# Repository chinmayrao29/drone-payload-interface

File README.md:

# Drone Payload Interface

A plug-and-play USB-C interface for hot-swapping payload modules on a drone. The drone carries an **interface board**. Each payload is a self-contained **module** that plugs into it over USB-C. When a module is connected, the interface board identifies it, checks it's a known and valid module, and only then switches power on to it.

The first payload module is a **LoRa communications relay**.

## How module identification works

Each module is identified in two independent ways, and power is enabled only when they agree:

1. **Analog ID (CC1 line):** the interface board has a fixed pull-up resistor on CC1. Each module type has its own pull-down resistor, so each type produces a distinct CC1 voltage that the ESP32 reads with its ADC.
2. **Digital ID (EEPROM):** each module carries an I2C EEPROM holding a module profile record. The interface board reads it over the USB-C SBU1/SBU2 pins (used as I2C SDA/SCL).

If the two channels disagree, or either one is unreadable, the module is not powered.

## Repository layout

```
drone-payload-interface/
├── firmware/
│   ├── interface-board-esp32/   ESP32-S3 firmware (PlatformIO)
│   └── relay-module-stm32/      STM32F103 relay firmware (STM32CubeIDE)
├── hardware/
│   └── interface_board/         KiCad: interface board
│       ├── relay_module/        KiCad: LoRa relay module
│       ├── test_module/         KiCad: test module
│       └── libs/                Bundled custom footprints (shared)
├── tools/
│   └── eeprom-programmer/       Arduino sketch for writing module EEPROMs
├── raspberry-pi/                Companion computer code (to be added)
└── docs/                        Bring-up notes and project documentation
```

## Hardware

### Interface board

| Part | Role |
|---|---|
| ESP32-S3-WROOM-1 | Main controller: detection, ID validation, power control, comms |
| GCT USB4085-GF-A | USB-C receptacle that modules plug into |
| TPS2116 | Power mux |
| INA219 | Current/voltage monitoring of module power |
| AMS1117-3.3 | 3.3 V regulator for the board logic |

**Headers**

| Header | Pins | Use |
|---|---|---|
| J1 | 2-pin | Power input (5 V) |
| J4 | 4-pin: GND / +3V3 / UART_TX / UART_RX | Debug and flashing (ESP32 UART) |
| J3 | 4-pin, same pinout as J4 | Link to the Raspberry Pi |

### Relay module

| Part | Role |
|---|---|
| STM32F103C8T6 | Module controller |
| EBYTE E22-900M30S | SX1262-based LoRa radio, 868 MHz, up to 30 dBm |
| TLV62568 + SRP4020TA-2R2M | Buck converter for the module supply |
| AT24Cxx EEPROM | Module ID profile, read by the interface board |
| SMA connector | Antenna |

> ⚠️ **Never power the relay module without an antenna attached.** The E22-900M30S transmits at up to 30 dBm, and transmitting into an open connector can damage its power amplifier.

## Firmware

### Interface board (ESP32-S3, PlatformIO)

Source is in `firmware/interface-board-esp32/src/`:

| File | Purpose |
|---|---|
| `main.cpp` | Startup and main loop |
| `detection.cpp/.h` | Module detection and CC1 / EEPROM ID checks |
| `power.cpp/.h` | Module power switching and monitoring |
| `comms.cpp/.h` | Communication with the Raspberry Pi |

**Build:** open `firmware/interface-board-esp32` as a folder in VS Code with the PlatformIO extension, then click **Build (✓)**.

**Flash over J4** using a USB-to-TTL adapter (CP2102 or similar):

| Adapter | J4 |
|---|---|
| GND | GND (pin 1) |
| TXD | UART_RX (pin 4) |
| RXD | UART_TX (pin 3) |
| 3V3 / 5V | not connected (the board is powered from J1) |

J4 has no DTR/RTS lines, so the ESP32 can't be put into bootloader mode automatically. Hold **GPIO0 low while powering up** the board, release it, then click **Upload (→)** in PlatformIO.

Serial monitor: 115200 baud.

### Relay module (STM32F103, STM32CubeIDE)

The project is in `firmware/relay-module-stm32/`. It uses the STM32 HAL with USART1, I2C1, SPI1 (to the radio) and TIM2 (1 Hz heartbeat). Received LoRa packets are signalled to the MCU through an EXTI interrupt on the radio's DIO line. The SX126x driver is in `Core/` and `sx126x_driver/`.

**Open:** in STM32CubeIDE, use **File → Import → Existing Projects into Workspace**, select `firmware/relay-module-stm32`, and leave "Copy projects into workspace" unticked.

**Flash:** connect an ST-Link V2 to the module's SWD header (SWDIO, SWCLK, GND, 3V3), then use Run/Debug in CubeIDE, or load `Debug/Relay_module.elf` in STM32CubeProgrammer.

### EEPROM programmer

`tools/eeprom-programmer/` contains an Arduino sketch for writing module profile records to the module EEPROMs. Open the `.ino` in the Arduino IDE. Check that the EEPROM type set in the sketch matches the chip fitted on the module before writing.

## Hardware design files

KiCad projects are in `hardware/interface_board/`. Custom footprints are bundled in the repo:

- `libs/Custom.pretty`: USB4085 USB-C connector, SRP4020 inductor, logo
- `relay_module/libs/E22-900M30S`: E22 radio footprint, symbol and 3D model

These are referenced through each project's `fp-lib-table` with `${KIPRJMOD}` paths, so the projects open on any machine without extra library setup. Gerbers and BOM/placement files for manufacturing are in each board's folder.

## Working with this repo

KiCad's local history (`.history/`), build output (`Debug/`, `.pio/`) and backup folders are excluded by `.gitignore`.

```
git add .
git commit -m "Describe the change"
git push
```

## Status

- Relay module firmware builds and flashes over ST-Link.
- Interface board powers up from J1, and the 3.3 V rail is confirmed.
- Next: confirm the ESP32 boots over the J4 serial link, then flash the interface board firmware.

See `docs/bring-up-notes.md` for details.

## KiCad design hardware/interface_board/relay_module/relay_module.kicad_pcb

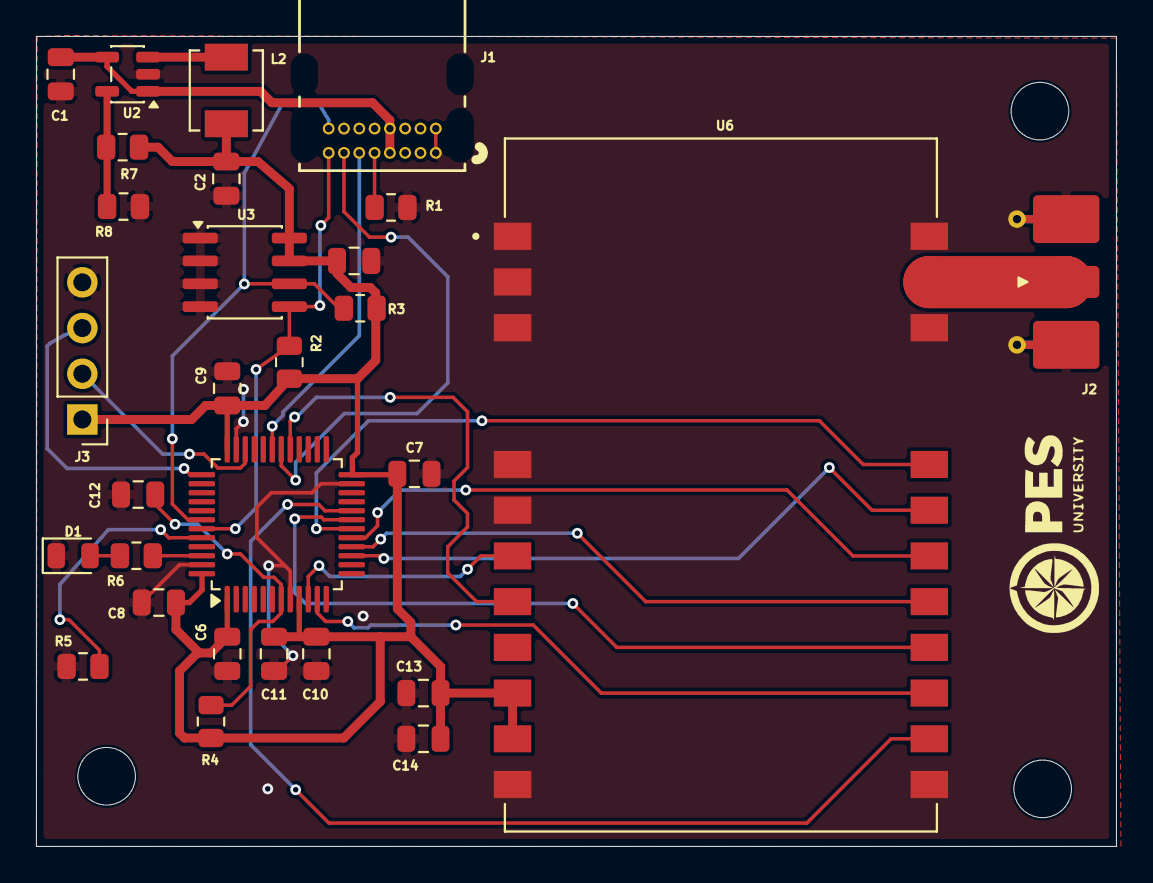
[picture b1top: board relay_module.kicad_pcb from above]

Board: 2 copper layers, 60.0 x 45.0 mm, 29 parts (0 on the bottom side), 26 nets.

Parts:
C1: 4.7u; C_0805_2012Metric
C2, C10, C13: 10u; C_0805_2012Metric
C5, C6, C7, C8, C9, C11, C12, C14: 100n; C_0805_2012Metric
D1: Green; LED_0805_2012Metric
J1: USB_C_Receptacle; CONN16_USB4085-GF-A_GCT
J2: SMA; SMA_Molex_73251-2120_EdgeMount_Horizontal
J3: Conn_01x04; PinHeader_1x04_P2.54mm_Vertical
L2: SRP4020TA-2R2M; IND_SRP4020TA-2R2M
R1: 220k; R_0805_2012Metric
R2, R3: 4.7k; R_0805_2012Metric
R4, R5, R8: 10k; R_0805_2012Metric
R6: 330; R_0805_2012Metric
R7: 33.2k; R_0805_2012Metric
U1: STM32F103C8Tx; LQFP-48_7x7mm_P0.5mm
U2: TLV62568DBV; SOT-23-5
U3: 24C02Cx-x-SN; SOIC-8_3.9x4.9mm_P1.27mm
U6: E22-900M30S; XCVR_E22-900M30S

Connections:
+3V3: C2.1, C5.1, C6.1, C7.1, C8.1, C9.1, C10.1, C11.1, C13.1, C14.1, J3.1, L2.2, R2.2, R3.2, R4.1, R7.2, U1.1 (VBAT), U1.9 (VDDA), U1.24 (VDD), U1.36 (VDD), U1.48 (VDD), U3.7 (WP), U3.8 (VCC), U6.9 (VCC), U6.10 (VCC)
/BUSY: U1.11 (PA1), U6.14 (BUSY)
/CC1_ID: J1.A5 (CC1), R1.1
/I2C_SCL: J1.B8 (SBU2), R3.1, U1.42 (PB6), U3.6 (SCL)
/I2C_SDA: J1.A8 (SBU1), R2.1, U1.43 (PB7), U3.5 (SDA)
/LORA_DIO1: U1.20 (PB2), U6.13 (DIO1)
/LORA_MISO: U1.16 (PA6), U6.16 (MISO)
/LORA_MOSI: U1.17 (PA7), U6.17 (MOSI)
/LORA_NSS: U1.18 (PB0), U6.19 (NSS)
/LORA_RESET: U1.19 (PB1), U6.15 (~RST)
/LORA_RXEN: U1.10 (PA0), U6.6 (RXEN)
/LORA_SCK: U1.15 (PA5), U6.18 (SCK)
/PA_TXEN: U1.29 (PA8), U6.7 (TXEN)
/SWDCK: J3.3, U1.37 (PA14)
/SWDIO: J3.2, U1.34 (PA13)
/UART_RX: J1.A6 (D+), U1.31 (PA10)
/UART_TX: J1.A7 (D-), U1.30 (PA9)
GND: C1.2, C2.2, C5.2, C6.2, C7.2, C8.2, C9.2, C10.2, C11.2, C12.2, C13.2, C14.2, D1.1 (K), J1.A1 (GND), J1.B1 (GND), J2.2, J3.4, R1.2, R5.1, R8.2, U1.8 (VSSA), U1.23 (VSS), U1.35 (VSS), U1.47 (VSS), U2.2 (GND), U3.1 (A0), U3.2 (A1), U3.3 (A2), U3.4 (GND), U6.1 (GND), U6.2 (GND), U6.3 (GND), U6.4 (GND), U6.5 (GND), U6.11 (GND), U6.12 (GND), U6.20 (GND), U6.22 (GND)
unnamed: D1.2 (A), R6.1
unnamed: J2.1, U6.21 (ANT)
unnamed: R5.2, U1.44 (BOOT0)
unnamed: C12.1, R4.2, U1.7 (NRST)
unnamed: R6.2, U1.46 (PB9)
unnamed: R7.1, R8.1, U2.5 (FB)
unnamed: L2.1, U2.3 (SW)
VBUS: C1.1, J1.A4 (VBUS), J1.B4 (VBUS), U2.1 (EN), U2.4 (VIN)

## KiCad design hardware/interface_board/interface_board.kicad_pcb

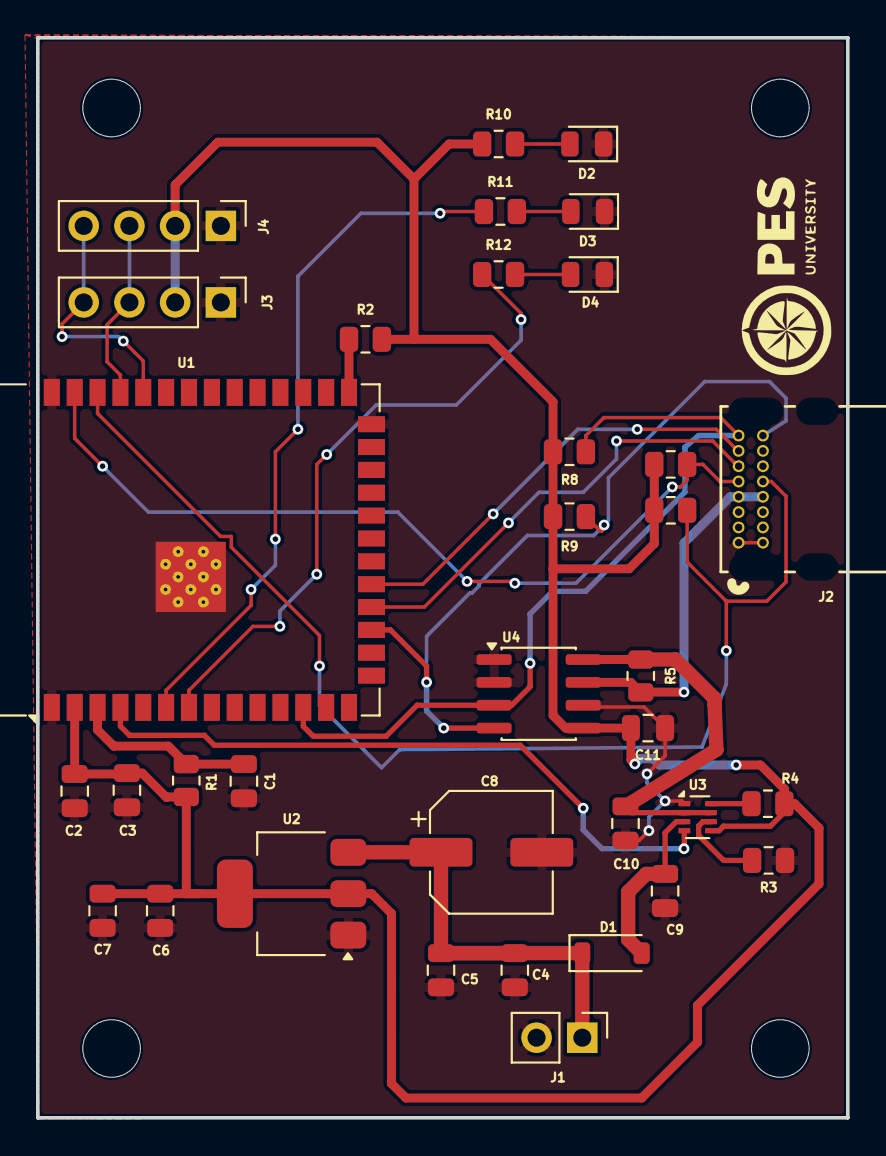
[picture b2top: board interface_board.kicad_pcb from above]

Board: 2 copper layers, 45.0 x 60.0 mm, 35 parts (0 on the bottom side), 24 nets.

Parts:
C1, C2, C4, C6, C9, C10, C11: 100n; C_0805_2012Metric
C3, C5, C7: 10u; C_0805_2012Metric
C8: 100u; CP_Elec_6.3x5.4
D1: 1N5819; D_SOD-123
D2, D3, D4: LED; LED_0805_2012Metric
J1: Conn_01x02; PinHeader_1x02_P2.54mm_Vertical
J2: USB_C_Receptacle; CONN16_USB4085-GF-A_GCT
J3, J4: Conn_01x04; PinHeader_1x04_P2.54mm_Vertical
R1, R2: 10k; R_0805_2012Metric
R3, R4: 100k; R_0805_2012Metric
R5: 0.1; R_0805_2012Metric
R6, R7: 5k1; R_0805_2012Metric
R8, R9: 4k7; R_0805_2012Metric
R10, R11, R12: 330; R_0805_2012Metric
U1: ESP32-S3-WROOM-1
U2: AMS1117-3.3; SOT-223-3_TabPin2
U3: TPS2116DRL; SOT-583-8
U4: INA219AxD; SOIC-8_3.9x4.9mm_P1.27mm

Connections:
+3V3: C2.1, C3.1, C6.1, C7.1, C11.1, J3.2, J4.2, R1.2, R2.2, R4.2, R6.2, R7.2, R8.2, R9.2, R10.1, U1.2 (3V3), U2.2 (VO), U3.5 (MODE), U4.5 (VS)
+5V: C9.1, D1.2 (A), U3.3 (VIN1)
/+5V From BEC: C4.1, C5.1, C8.1, D1.1 (K), J1.1, U2.3 (VI)
/CC1_ADC: J2.A5 (CC1), R6.1, U1.39 (IO1)
/CC2_ADC: J2.B5 (CC2), R7.1, U1.38 (IO2)
/ESP_I06: R11.1, U1.6 (IO6)
/ESP_I07: R12.1, U1.7 (IO7)
/ESP_PWR_EN: U1.4 (IO4), U3.4 (PR1)
/I2C_SCL: J2.B8 (SBU2), R9.1, U1.17 (IO9), U4.4 (SCL)
/I2C_SDA: J2.A8 (SBU1), R8.1, U1.12 (IO8), U4.3 (SDA)
/MOD_RX: J2.A7 (D-), U1.19 (IO11)
/MOD_TX: J2.A6 (D+), U1.18 (IO10)
/UART_RX: J3.4, J4.4, U1.36 (RXD0)
/UART_TX: J3.3, J4.3, U1.37 (TXD0)
/VBUS: C10.1, R5.1, U3.2 (VOUT), U3.7 (VOUT), U4.8 (IN+)
/VBUS_OUT: J2.A4 (VBUS), J2.B4 (VBUS), R5.2, U4.7 (IN-)
GND: C1.2, C2.2, C3.2, C4.2, C5.2, C6.2, C7.2, C8.2, C9.2, C10.2, C11.2, D2.1 (K), D3.1 (K), D4.1 (K), J1.2, J2.A1 (GND), J2.B1 (GND), J3.1, J4.1, R3.2, U1.1 (GND), U1.26 (IO45), U1.40 (GND), U1.41 (GND), U2.1 (GND), U3.1 (GND), U4.1 (A1), U4.2 (A0), U4.6 (GND)
unnamed: D2.2 (A), R10.2
unnamed: D3.2 (A), R11.2
unnamed: D4.2 (A), R12.2
unnamed: C1.1, R1.1, U1.3 (EN)
unnamed: R2.1, U1.27 (IO0)
unnamed: R4.1, U3.8 (ST)
unnamed: R3.1, U3.6 (VIN2)

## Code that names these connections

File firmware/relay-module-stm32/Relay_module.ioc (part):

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Mcu.Name=STM32F103C(8-B)Tx
Mcu.Package=LQFP48
Mcu.UserName=STM32F103C8Tx
PA0-WKUP.GPIOParameters=GPIO_Label
PA0-WKUP.GPIO_Label=LORA_RXEN
PA0-WKUP.Signal=GPIO_Input
PA1.GPIOParameters=GPIO_Label
PA1.GPIO_Label=LORA_BUSY
PA1.Signal=GPIO_Input
PA10.Mode=Asynchronous
PA10.Signal=USART1_RX
PA13.Mode=Serial_Wire
PA13.Signal=SYS_JTMS-SWDIO
PA14.Mode=Serial_Wire
PA14.Signal=SYS_JTCK-SWCLK
PA5.Mode=Full_Duplex_Master
PA5.Signal=SPI1_SCK
PA6.Mode=Full_Duplex_Master
PA6.Signal=SPI1_MISO
PA7.Mode=Full_Duplex_Master
PA7.Signal=SPI1_MOSI
PA8.GPIOParameters=GPIO_Label
PA8.GPIO_Label=PA_TXEN
PA8.Signal=GPIO_Output
PA9.Mode=Asynchronous
PA9.Signal=USART1_TX
PB0.GPIOParameters=GPIO_Label
PB0.GPIO_Label=LORA_NSS
PB0.Signal=GPIO_Output
PB1.GPIOParameters=GPIO_Label
PB1.GPIO_Label=LORA_RESET
PB1.Signal=GPIO_Output
PB3.GPIOParameters=GPIO_Label
PB3.GPIO_Label=LORA_DIO1
PB3.Signal=GPXTI3
PB6.Mode=I2C
PB6.Signal=I2C1_SCL
PB7.Mode=I2C
PB7.Signal=I2C1_SDA
PB8.GPIOParameters=GPIO_Label
PB8.GPIO_Label=HEARTBEAT
PB8.Signal=GPIO_Output
board=custom

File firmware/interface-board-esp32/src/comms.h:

#pragma once
#include <Arduino.h>

// UART pins
#define PIN_UART_TX     43
#define PIN_UART_RX     44
#define PIN_MOD_TX      10
#define PIN_MOD_RX      11

// UART baud rates
#define PI_BAUD         115200
#define MODULE_BAUD     115200

void comms_init();
void comms_send_pi(const char* message);
void comms_send_module(const char* message);
String comms_read_pi();
String comms_read_module();
void comms_poll();

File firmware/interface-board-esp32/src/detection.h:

#pragma once
#include <Arduino.h>
#include <Wire.h>

// ADC pins
#define PIN_CC1_ADC     1
#define PIN_CC2_ADC     2

// I2C pins
#define PIN_I2C_SDA     8
#define PIN_I2C_SCL     9

// Heartbeat pin
#define PIN_HEARTBEAT   5

// EEPROM address
#define EEPROM_ADDR     0x50

// Module type IDs
#define MODULE_UNKNOWN          0xFF
#define MODULE_TEST             0x00
#define MODULE_THERMAL          0x01
#define MODULE_SPRAY            0x02
#define MODULE_LIDAR            0x03
#define MODULE_GRIPPER          0x04
#define MODULE_CAMERA           0x05
#define MODULE_RELAY            0x06
#define MODULE_TETHER           0x07
// Module profile from EEPROM
struct __attribute__((packed)) ModuleProfile {
    uint8_t typeId;
    uint8_t hwVersion;
    uint8_t fwVersion;
    uint16_t maxCurrentMa;
    uint8_t baudCode;
    uint8_t reserved[2];
    char name[24];
};

// State machine states
typedef enum {
  STATE_IDLE,
  STATE_DETECTION,
  STATE_RUNNING,
  STATE_FAULT
} SystemState;

extern SystemState currentState;
extern ModuleProfile currentModule;
extern uint16_t maxCurrentMa;

void detection_init();
float read_cc1_voltage();
uint8_t identify_module(float voltage);
bool read_eeprom(ModuleProfile* profile);
void idle_loop();
void detection_loop();
void running_loop();
void fault_loop();
